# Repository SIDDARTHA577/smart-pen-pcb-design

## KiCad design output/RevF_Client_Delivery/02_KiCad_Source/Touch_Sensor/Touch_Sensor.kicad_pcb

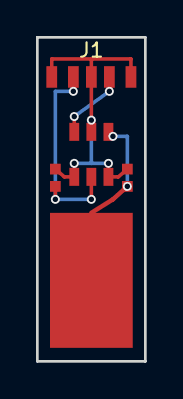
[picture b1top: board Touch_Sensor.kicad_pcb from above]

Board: 2 copper layers, 6.0 x 18.0 mm, 5 parts (0 on the bottom side), 4 nets.

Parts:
C1: 0.1uF; C_0402
C2: 10pF; C_0402
E1: TOUCH_PAD; Touch_Pad_5x10mm
J1: SM03B-SRSS-TB; JST_SH_3P
U1: TTP223-BA6; SOT-23-6

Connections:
3V3: C1.1, J1.1, U1.5
GND: C1.2, C2.2, J1.2, J1.4, U1.2, U1.4, U1.6
TOUCH_IN: C2.1, E1.1, U1.3
TOUCH_OUT: J1.3, U1.1

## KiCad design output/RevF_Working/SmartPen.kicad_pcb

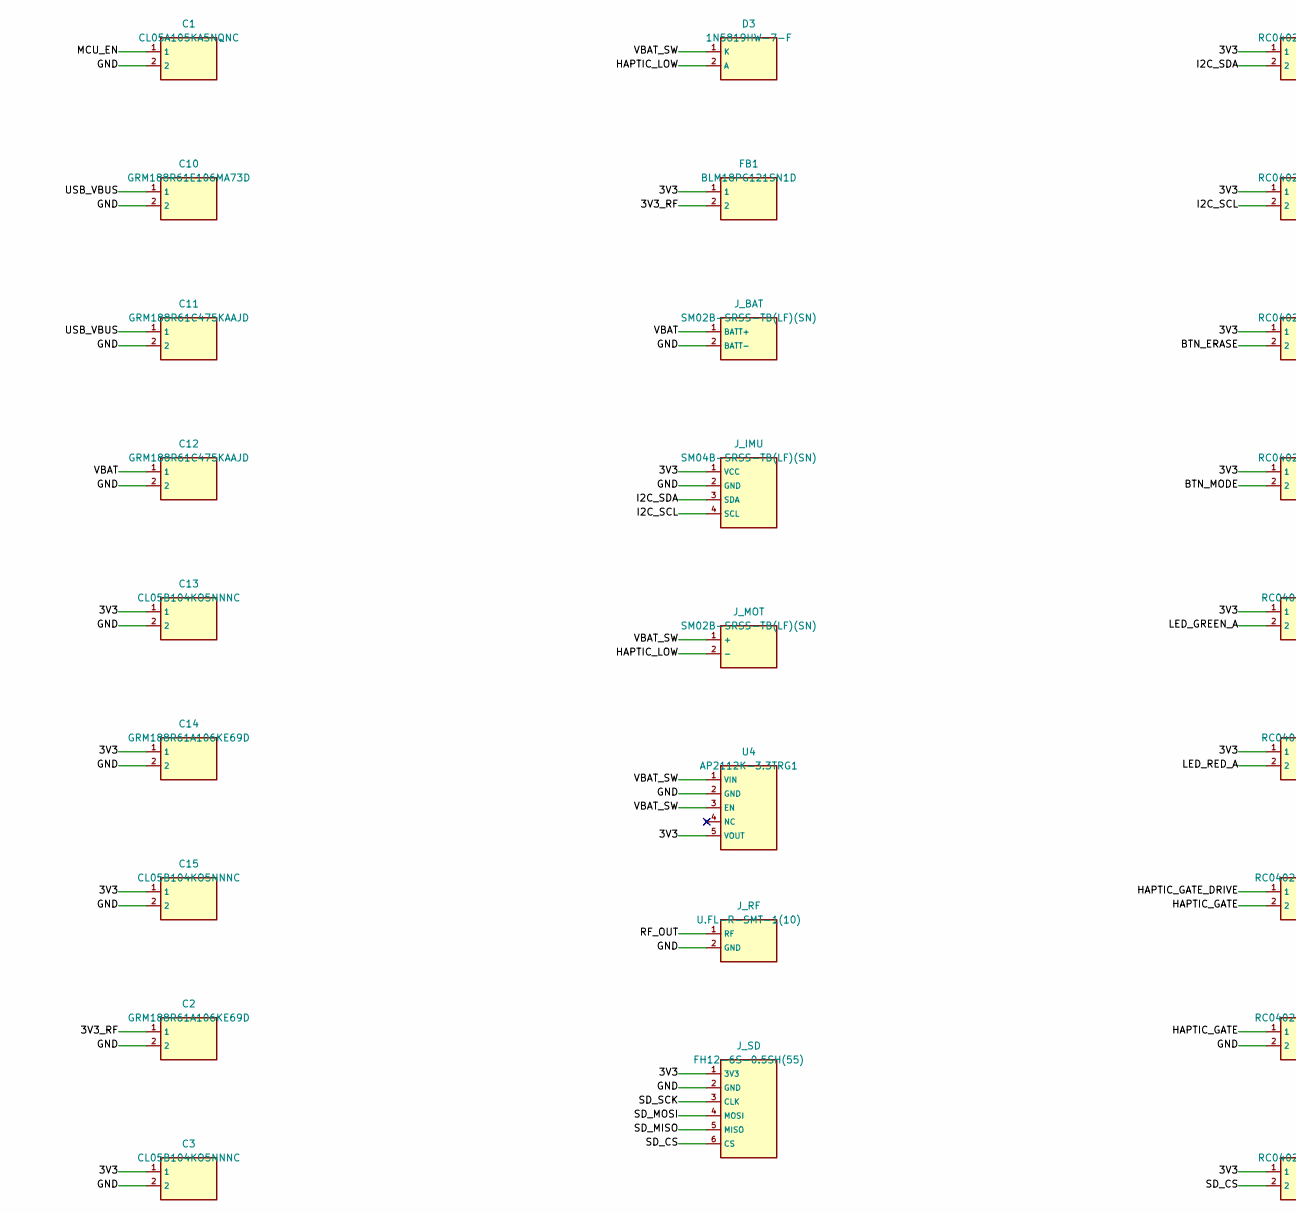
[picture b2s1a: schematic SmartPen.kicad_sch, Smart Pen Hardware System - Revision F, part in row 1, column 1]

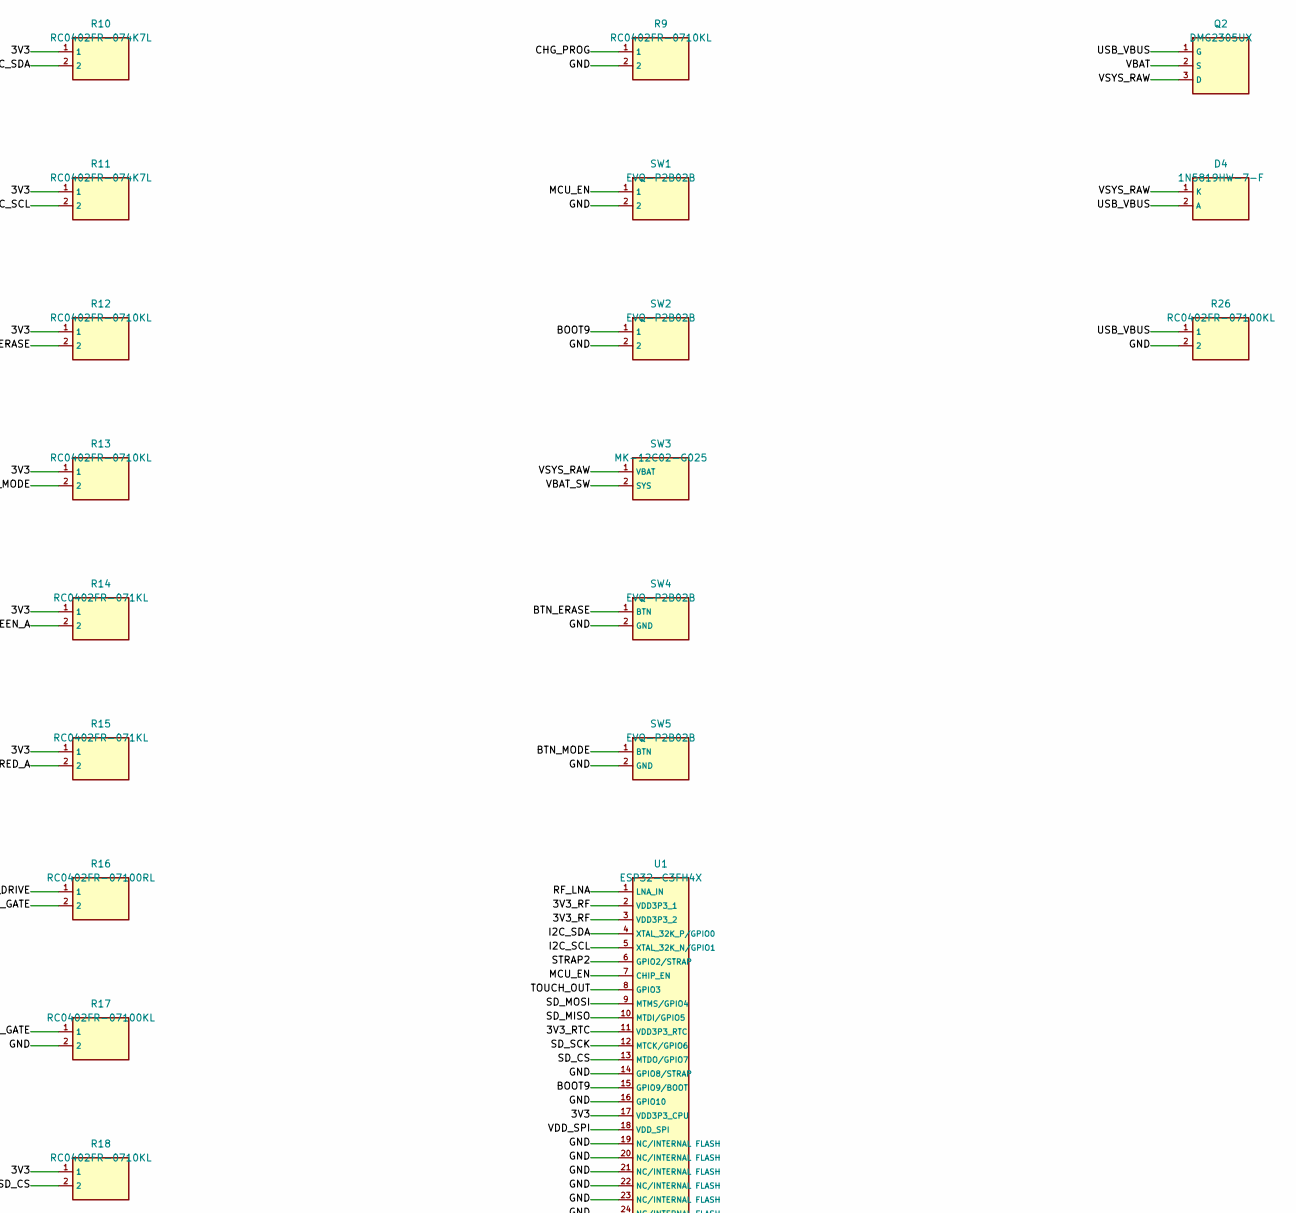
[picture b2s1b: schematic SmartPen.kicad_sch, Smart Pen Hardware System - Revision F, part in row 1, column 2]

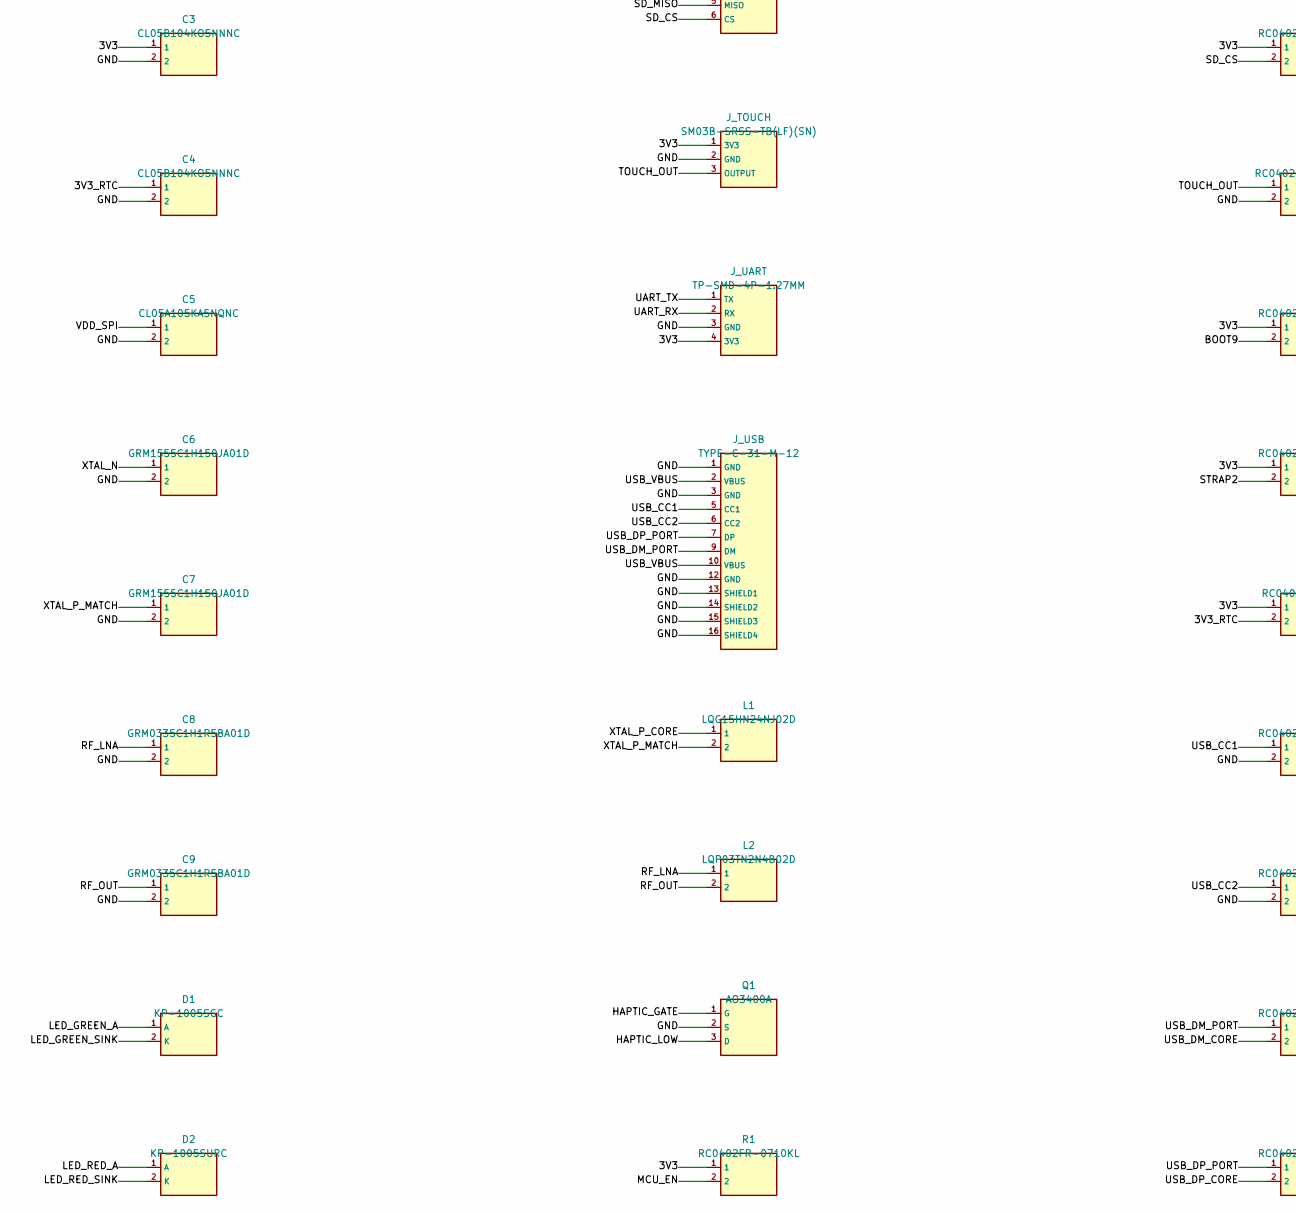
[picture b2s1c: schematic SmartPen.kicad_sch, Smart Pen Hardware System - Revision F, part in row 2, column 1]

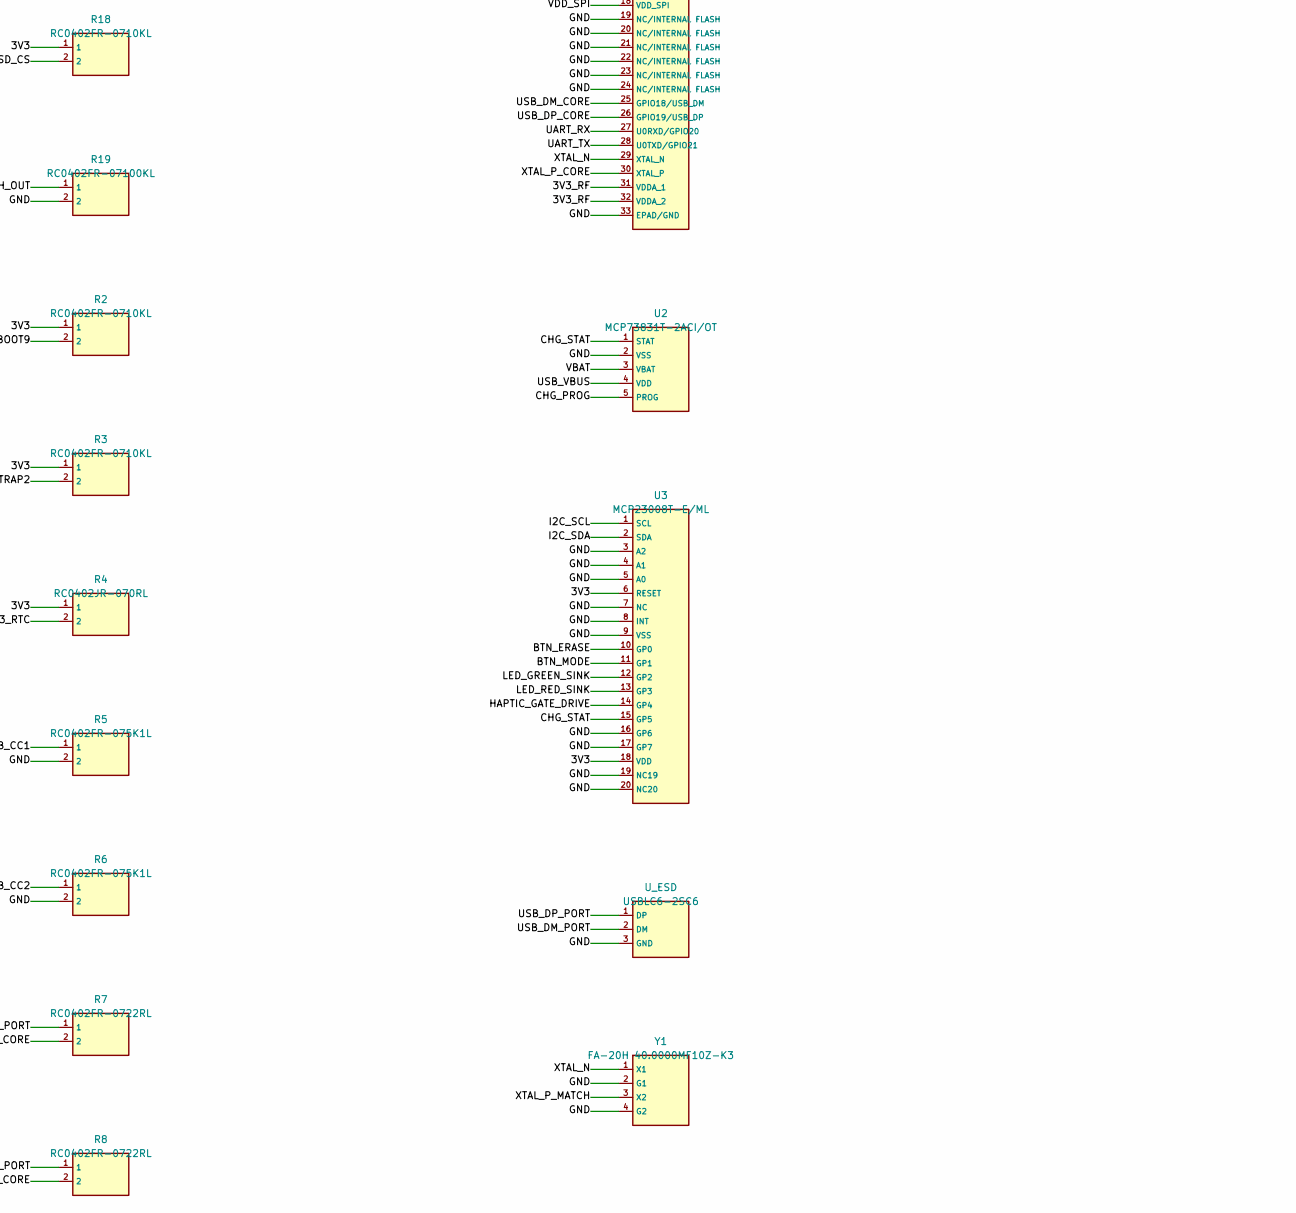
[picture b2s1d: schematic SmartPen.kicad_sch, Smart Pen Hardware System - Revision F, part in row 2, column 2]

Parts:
C1: CL05A105KA5NQNC; C1
C2: GRM188R61A106KE69D; C2
C3: CL05B104KO5NNNC; C3
C4: CL05B104KO5NNNC; C4
C5: CL05A105KA5NQNC; C5
C6: GRM1555C1H150JA01D; C6
C7: GRM1555C1H150JA01D; C7
C8: GRM0335C1H1R5BA01D; C8
C9: GRM0335C1H1R5BA01D; C9
C10: GRM188R61E106MA73D; C10
C11: GRM188R61C475KAAJD; C11
C12: GRM188R61C475KAAJD; C12
C13: CL05B104KO5NNNC; C13
C14: GRM188R61A106KE69D; C14
C15: CL05B104KO5NNNC; C15
D1: KP-1005SGC; D1
D2: KP-1005SURC; D2
D3, D4: 1N5819HW-7-F; D3
FB1: BLM18PG121SN1D; FB1
J_BAT: SM02B-SRSS-TB(LF)(SN); J_BAT
J_IMU: SM04B-SRSS-TB(LF)(SN); J_IMU
J_MOT: SM02B-SRSS-TB(LF)(SN); J_MOT
J_RF: U.FL-R-SMT-1(10); J_RF
J_SD: FH12-6S-0.5SH(55); J_SD
J_TOUCH: SM03B-SRSS-TB(LF)(SN); J_TOUCH
J_UART: TP-SMD-4P-1.27MM; J_UART
J_USB: TYPE-C-31-M-12; J_USB
L1: LQG15HN24NJ02D; L1
L2: LQP03TN2N4B02D; L2
Q1: AO3400A; Q1
Q2: DMG2305UX; Q1
R1: RC0402FR-0710KL; R1
R2: RC0402FR-0710KL; R2
R3: RC0402FR-0710KL; R3
R4: RC0402JR-070RL; R4
R5: RC0402FR-075K1L; R5
R6: RC0402FR-075K1L; R6
R7: RC0402FR-0722RL; R7
R8: RC0402FR-0722RL; R8
R9: RC0402FR-0710KL; R9
R10: RC0402FR-074K7L; R10
R11: RC0402FR-074K7L; R11
R12: RC0402FR-0710KL; R12
R13: RC0402FR-0710KL; R13
R14: RC0402FR-071KL; R14
R15: RC0402FR-071KL; R15
R16: RC0402FR-07100RL; R16
R17: RC0402FR-07100KL; R17
R18: RC0402FR-0710KL; R18
R19: RC0402FR-07100KL; R19
R26: RC0402FR-07100KL; R1
SW1: EVQ-P2B02B; SW1
SW2: EVQ-P2B02B; SW2
SW3: MK-12C02-G025; SW3
SW4: EVQ-P2B02B; SW4
SW5: EVQ-P2B02B; SW5
U1: ESP32-C3FH4X; U1
U2: MCP73831T-2ACI/OT; U2
U3: MCP23008T-E/ML; U3
U4: AP2112K-3.3TRG1; J_PWR
U_ESD: USBLC6-2SC6; U_ESD
Y1: FA-20H 40.0000MF10Z-K3; Y1

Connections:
/3V3: C3.1, C13.1, C14.1, C15.1, FB1.1, J_IMU.1 (VCC), J_SD.1 (3V3), J_TOUCH.1 (3V3), J_UART.4 (3V3), R1.1, R2.1, R3.1, R4.1, R10.1, R11.1, R12.1, R13.1, R14.1, R15.1, R18.1, U1.17 (VDD3P3_CPU), U3.6 (RESET), U3.18 (VDD), U4.5 (VOUT); also elsewhere on the board
/3V3_RF: C2.1, FB1.2, U1.2 (VDD3P3_1), U1.3 (VDD3P3_2), U1.31 (VDDA_1), U1.32 (VDDA_2)
/3V3_RTC: C4.1, R4.2, U1.11 (VDD3P3_RTC)
/BOOT9: R2.2, SW2.1, U1.15 (GPIO9/BOOT)
/BTN_ERASE: R12.2, SW4.1 (BTN), U3.10 (GP0)
/BTN_MODE: R13.2, SW5.1 (BTN), U3.11 (GP1)
/CHG_PROG: R9.1, U2.5 (PROG)
/CHG_STAT: U2.1 (STAT), U3.15 (GP5)
/GND: C1.2, C2.2, C3.2, C4.2, C5.2, C6.2, C7.2, C8.2, C9.2, C10.2, C11.2, C12.2, C13.2, C14.2, C15.2, J_BAT.2 (BATT-), J_BAT.3, J_BAT.4, J_IMU.2 (GND), J_MOT.3, J_MOT.4, J_RF.2 (GND), J_RF.3, J_SD.2 (GND), J_TOUCH.2 (GND), J_UART.3 (GND), J_USB.1 (GND), J_USB.3 (GND), J_USB.12 (GND), J_USB.13 (SHIELD1), J_USB.14 (SHIELD2), J_USB.15 (SHIELD3), J_USB.16 (SHIELD4), Q1.2 (S), R5.2, R6.2, R9.2, R17.2, R19.2, R26.2, SW1.2, SW2.2, SW3.3, SW4.2 (GND), SW5.2 (GND), U1.14 (GPIO8/STRAP), U1.16 (GPIO10), U1.19 (NC/INTERNAL FLASH), U1.20 (NC/INTERNAL FLASH), U1.21 (NC/INTERNAL FLASH), U1.22 (NC/INTERNAL FLASH), U1.23 (NC/INTERNAL FLASH), U1.24 (NC/INTERNAL FLASH), U1.33 (EPAD/GND), U2.2 (VSS), U3.3 (A2), U3.4 (A1), U3.5 (A0), U3.7 (NC), U3.8 (INT), U3.9 (VSS), U3.16 (GP6), U3.17 (GP7), U3.19 (NC19), U3.20 (NC20), U3.21, U4.2 (GND), U_ESD.3 (GND), Y1.2 (G1), Y1.4 (G2); also elsewhere on the board
/HAPTIC_GATE: Q1.1 (G), R16.2, R17.1
/HAPTIC_GATE_DRIVE: R16.1, U3.14 (GP4)
/HAPTIC_LOW: D3.2 (A), J_MOT.2 (-), Q1.3 (D)
/I2C_SCL: J_IMU.4 (SCL), R11.2, U1.5 (XTAL_32K_N/GPIO1), U3.1 (SCL)
/I2C_SDA: J_IMU.3 (SDA), R10.2, U1.4 (XTAL_32K_P/GPIO0), U3.2 (SDA)
/LED_GREEN_A: D1.1 (A), R14.2
/LED_GREEN_SINK: D1.2 (K), U3.12 (GP2)
/LED_RED_A: D2.1 (A), R15.2
/LED_RED_SINK: D2.2 (K), U3.13 (GP3)
/MCU_EN: C1.1, R1.2, SW1.1, U1.7 (CHIP_EN)
/RF_LNA: C8.1, L2.1, U1.1 (LNA_IN)
/RF_OUT: C9.1, J_RF.1 (RF), L2.2
/SD_CS: J_SD.6 (CS), R18.2, U1.13 (MTDO/GPIO7)
/SD_MISO: J_SD.5 (MISO), U1.10 (MTDI/GPIO5)
/SD_MOSI: J_SD.4 (MOSI), U1.9 (MTMS/GPIO4)
/SD_SCK: J_SD.3 (CLK), U1.12 (MTCK/GPIO6)
/STRAP2: R3.2, U1.6 (GPIO2/STRAP)
/TOUCH_OUT: J_TOUCH.3 (OUTPUT), R19.1, U1.8 (GPIO3)
/UART_RX: J_UART.2 (RX), U1.27 (U0RXD/GPIO20)
/UART_TX: J_UART.1 (TX), U1.28 (U0TXD/GPIO21)
/USB_CC1: J_USB.5 (CC1), R5.1
/USB_CC2: J_USB.6 (CC2), R6.1
/USB_DM_CORE: R7.2, U1.25 (GPIO18/USB_DM), U_ESD.4
/USB_DM_PORT: J_USB.9 (DM), R7.1, U_ESD.2 (DM)
/USB_DP_CORE: R8.2, U1.26 (GPIO19/USB_DP), U_ESD.6
/USB_DP_PORT: J_USB.7 (DP), R8.1, U_ESD.1 (DP)
/USB_VBUS: C10.1, C11.1, D4.2 (A), J_USB.2 (VBUS), J_USB.10 (VBUS), Q2.1 (G), R26.1, U2.4 (VDD), U_ESD.5
/VBAT_SW: D3.1 (K), J_MOT.1 (+), SW3.2 (SYS), U4.1 (VIN), U4.3 (EN); also elsewhere on the board
/VDD_SPI: C5.1, U1.18 (VDD_SPI)
/XTAL_N: C6.1, U1.29 (XTAL_N), Y1.1 (X1)
/XTAL_P_CORE: L1.1, U1.30 (XTAL_P)
/XTAL_P_MATCH: C7.1, L1.2, Y1.3 (X2)

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
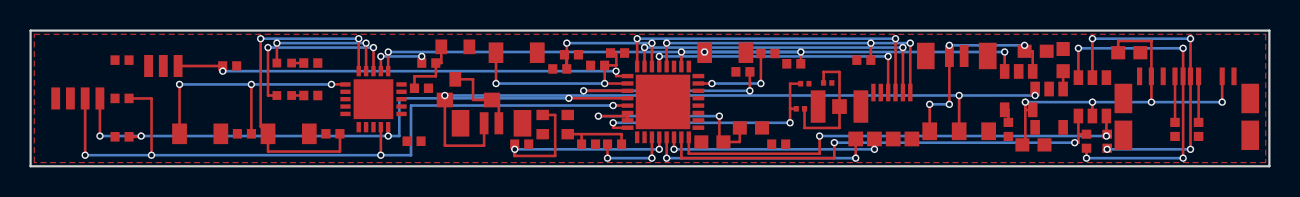
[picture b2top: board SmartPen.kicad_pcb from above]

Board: 2 copper layers, 84.0 x 9.2 mm, 60 parts (0 on the bottom side), 42 nets.

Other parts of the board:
J_PWR: AP2112K-3.3TRG1; J_PWR

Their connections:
/3V3: J_PWR.3; also elsewhere on the board
/GND: J_PWR.2, J_PWR.4, J_PWR.5; also elsewhere on the board
/VBAT_SW: J_PWR.1; also elsewhere on the board

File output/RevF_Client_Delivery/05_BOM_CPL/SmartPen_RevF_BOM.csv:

Item,Reference,Value / Device,Package / Footprint,Manufacturer,Manufacturer Part Number,Description,Quantity
1,C1,1uF EN delay,C0402,Samsung Electro-Mechanics,CL05A105KA5NQNC,1uF EN delay for Smart Pen Rev F,1
2,C10,10uF USB VBUS bulk,C0603,Murata,GRM188R61E106MA73D,10uF USB VBUS bulk for Smart Pen Rev F,1
3,C11,4.7uF charger input cap,C0603,Murata,GRM188R61C475KAAJD,4.7uF charger input cap for Smart Pen Rev F,1
4,C12,4.7uF charger output cap,C0603,Murata,GRM188R61C475KAAJD,4.7uF charger output cap for Smart Pen Rev F,1
5,C13,0.1uF Expander bypass cap,C0402,Samsung,CL05B104KO5NNNC,0.1uF Expander bypass cap for Smart Pen Rev F,1
6,C14,10uF System 3.3V bulk cap,C0603,Murata,GRM188R61A106KE69D,10uF System 3.3V bulk cap for Smart Pen Rev F,1
7,C15,0.1uF Front IMU cable filter cap,C0402,Samsung,CL05B104KO5NNNC,0.1uF Front IMU cable filter cap for Smart Pen Rev F,1
8,C2,10uF RF bulk,C0603,Murata,GRM188R61A106KE69D,10uF RF bulk for Smart Pen Rev F,1
9,C3,0.1uF CPU bypass,C0402,Samsung,CL05B104KO5NNNC,0.1uF CPU bypass for Smart Pen Rev F,1
10,C4,0.1uF RTC bypass,C0402,Samsung,CL05B104KO5NNNC,0.1uF RTC bypass for Smart Pen Rev F,1
11,C5,1uF VDD_SPI bypass,C0402,Samsung,CL05A105KA5NQNC,1uF VDD_SPI bypass for Smart Pen Rev F,1
12,C6,15pF XTAL_N load cap,C0402,Murata,GRM1555C1H150JA01D,15pF XTAL_N load cap for Smart Pen Rev F,1
13,C7,15pF XTAL_P load cap,C0402,Murata,GRM1555C1H150JA01D,15pF XTAL_P load cap for Smart Pen Rev F,1
14,C8,1.5pF RF shunt cap,C0201,Murata,GRM0335C1H1R5BA01D,1.5pF RF shunt cap for Smart Pen Rev F,1
15,C9,1.5pF RF shunt cap,C0201,Murata,GRM0335C1H1R5BA01D,1.5pF RF shunt cap for Smart Pen Rev F,1
16,D1,Green SMD Mode LED,LED0402,Kingbright,KP-1005SGC,Green SMD Mode LED for Smart Pen Rev F,1
17,D2,Red SMD Mode LED,LED0402,Kingbright,KP-1005SURC,Red SMD Mode LED for Smart Pen Rev F,1
18,D3,Schottky Flyback Diode,SOD-123,Diodes Inc.,1N5819HW-7-F,Schottky Flyback Diode for Smart Pen Rev F,1
19,FB1,RF ferrite bead,L0603,Murata,BLM18PG121SN1D,RF ferrite bead for Smart Pen Rev F,1
20,J_BAT,2-Pin Keyed LiPo Battery Header,CONN-SMD_JST-SH-BM02B-SRSS,JST,SM02B-SRSS-TB(LF)(SN),2-Pin Keyed LiPo Battery Header for Smart Pen Rev F,1
21,J_IMU,4-Pin Keyed Front IMU Connector,CONN-SMD_JST-SH-4P-SM04B-SRSS,JST,SM04B-SRSS-TB(LF)(SN),4-Pin Keyed Front IMU Connector for Smart Pen Rev F,1
22,J_MOT,2-Pin Vibration Motor Connector / Pads,CONN-SMD_JST-SH-BM02B-SRSS,JST,SM02B-SRSS-TB(LF)(SN),2-Pin Vibration Motor Connector / Pads for Smart Pen Rev F,1
23,J_PWR,High-Current Low-Dropout 3.3V Regulator,SOT-23-5,Diodes Inc. / Micrel,AP2112K-3.3TRG1,High-Current Low-Dropout 3.3V Regulator for Smart Pen Rev F,1
24,J_RF,U.FL RF receptacle,CONN-SMD_U.FL-R-SMT,Hirose,U.FL-R-SMT-1(10),U.FL RF receptacle for Smart Pen Rev F,1
25,J_SD,MicroSD SPI 6-Pin FPC Connector,CONN-FPC_6P_P0.5mm_SMD,Hirose / Molex,FH12-6S-0.5SH(55),MicroSD SPI 6-Pin FPC Connector for Smart Pen Rev F,1
26,J_TOUCH,External Touch Controller / Electrode Header,CONN-SMD_JST-SH-3P-SM03B-SRSS,JST / TonTek,SM03B-SRSS-TB(LF)(SN),External Touch Controller / Electrode Header for Smart Pen Rev F,1
27,J_UART,4-Pin UART & Programming Test Pads,TESTPAD_4P_1x4_P1.27mm,RadixView / Custom SMD,TP-SMD-4P-1.27MM,4-Pin UART & Programming Test Pads for Smart Pen Rev F,1
28,J_USB,USB Type-C receptacle 16-pin,USB-C-SMD_16PIN_TYPE-C-31-M-12,Korean HRO / JLCPCB,TYPE-C-31-M-12,USB Type-C receptacle 16-pin for Smart Pen Rev F,1
29,L1,24nH clock harmonic filter,L0402,Murata,LQG15HN24NJ02D,24nH clock harmonic filter for Smart Pen Rev F,1
30,L2,2.4nH RF matching inductor,L0201,Murata,LQP03TN2N4B02D,2.4nH RF matching inductor for Smart Pen Rev F,1
31,Q1,N-Channel Logic MOSFET,SOT-23-3,Alpha & Omega,AO3400A,N-Channel Logic MOSFET for Smart Pen Rev F,1
32,R1,10k EN pullup,R0402,Yageo,RC0402FR-0710KL,10k EN pullup for Smart Pen Rev F,1
33,R10,4.7k I2C SDA pullup,R0402,Yageo,RC0402FR-074K7L,4.7k I2C SDA pullup for Smart Pen Rev F,1
34,R11,4.7k I2C SCL pullup,R0402,Yageo,RC0402FR-074K7L,4.7k I2C SCL pullup for Smart Pen Rev F,1
35,R12,10k ERASE button pullup,R0402,Yageo,RC0402FR-0710KL,10k ERASE button pullup for Smart Pen Rev F,1
36,R13,10k MODE button pullup,R0402,Yageo,RC0402FR-0710KL,10k MODE button pullup for Smart Pen Rev F,1
37,R14,1k Green LED current limit,R0402,Yageo,RC0402FR-071KL,1k Green LED current limit for Smart Pen Rev F,1
38,R15,1k Red LED current limit,R0402,Yageo,RC0402FR-071KL,1k Red LED current limit for Smart Pen Rev F,1
39,R16,100R Haptic gate resistor,R0402,Yageo,RC0402FR-07100RL,100R Haptic gate resistor for Smart Pen Rev F,1
40,R17,100k Haptic gate pulldown,R0402,Yageo,RC0402FR-07100KL,100k Haptic gate pulldown for Smart Pen Rev F,1
41,R18,10k MicroSD CS pullup,R0402,Yageo,RC0402FR-0710KL,10k MicroSD CS pullup for Smart Pen Rev F,1
42,R19,100k Touch pulldown option,R0402,Yageo,RC0402FR-07100KL,100k Touch pulldown option for Smart Pen Rev F,1
43,R2,10k GPIO9 pullup,R0402,Yageo,RC0402FR-0710KL,10k GPIO9 pullup for Smart Pen Rev F,1
44,R3,10k GPIO2 pullup,R0402,Yageo,RC0402FR-0710KL,10k GPIO2 pullup for Smart Pen Rev F,1
45,R4,0R RTC tie,R0402,Yageo,RC0402JR-070RL,0R RTC tie for Smart Pen Rev F,1
46,R5,5.1k CC1 pulldown,R0402,Yageo,RC0402FR-075K1L,5.1k CC1 pulldown for Smart Pen Rev F,1
47,R6,5.1k CC2 pulldown,R0402,Yageo,RC0402FR-075K1L,5.1k CC2 pulldown for Smart Pen Rev F,1
48,R7,22R USB D- series damping,R0402,Yageo,RC0402FR-0722RL,22R USB D- series damping for Smart Pen Rev F,1
49,R8,22R USB D+ series damping,R0402,Yageo,RC0402FR-0722RL,22R USB D+ series damping for Smart Pen Rev F,1
50,R9,"3.3k PROG resistor (303mA charge, safe <=1.0C)",R0402,Yageo,RC0402FR-073K3L,"3.3k PROG resistor (303mA charge, safe <=1.0C) for Smart Pen Rev F",1
51,SW1,RESET switch NO,SW-SMD_3.0x2.5mm,Panasonic / C&K,EVQ-P2B02B,RESET switch NO for Smart Pen Rev F,1
52,SW2,BOOT switch NO,SW-SMD_3.0x2.5mm,Panasonic / C&K,EVQ-P2B02B,BOOT switch NO for Smart Pen Rev F,1
53,SW3,SPDT Slide Power Switch,SW-SLIDE-SMD_MK12C02,C&K / Korean HRO,MK-12C02-G025,SPDT Slide Power Switch for Smart Pen Rev F,1
54,SW4,ERASE Tactile Button NO,SW-SMD_3.0x2.5mm,Panasonic / C&K,EVQ-P2B02B,ERASE Tactile Button NO for Smart Pen Rev F,1
55,SW5,MODE Tactile Button NO,SW-SMD_3.0x2.5mm,Panasonic / C&K,EVQ-P2B02B,MODE Tactile Button NO for Smart Pen Rev F,1
56,U1,ESP32-C3FH4X,QFN-32_5x5mm_P0.5mm_EP3.7mm,Espressif Systems,ESP32-C3FH4X,ESP32-C3FH4X for Smart Pen Rev F,1
57,U2,LiPo Linear Charger,SOT-23-5,Microchip,MCP73831T-2ACI/OT,LiPo Linear Charger for Smart Pen Rev F,1
58,U3,8-Bit I2C GPIO Expander,QFN-20_4x4mm_P0.5mm_EP2.7mm,Microchip,MCP23008T-E/ML,8-Bit I2C GPIO Expander for Smart Pen Rev F,1
59,U_ESD,USB ESD Protection Array,SOT-23-6,STMicroelectronics,USBLC6-2SC6,USB ESD Protection Array for Smart Pen Rev F,1
60,Y1,40MHz +/-10ppm Crystal,CRYSTAL-SMD_2.5x2.0mm_4P,Epson,FA-20H 40.0000MF10Z-K3,40MHz +/-10ppm Crystal for Smart Pen Rev F,1
